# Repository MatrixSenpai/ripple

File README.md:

# Ripple

A small temperature box featuring a small led display and neopixel ring.

SW licensed under MIT license.
HW licensed under CC BY-SA.

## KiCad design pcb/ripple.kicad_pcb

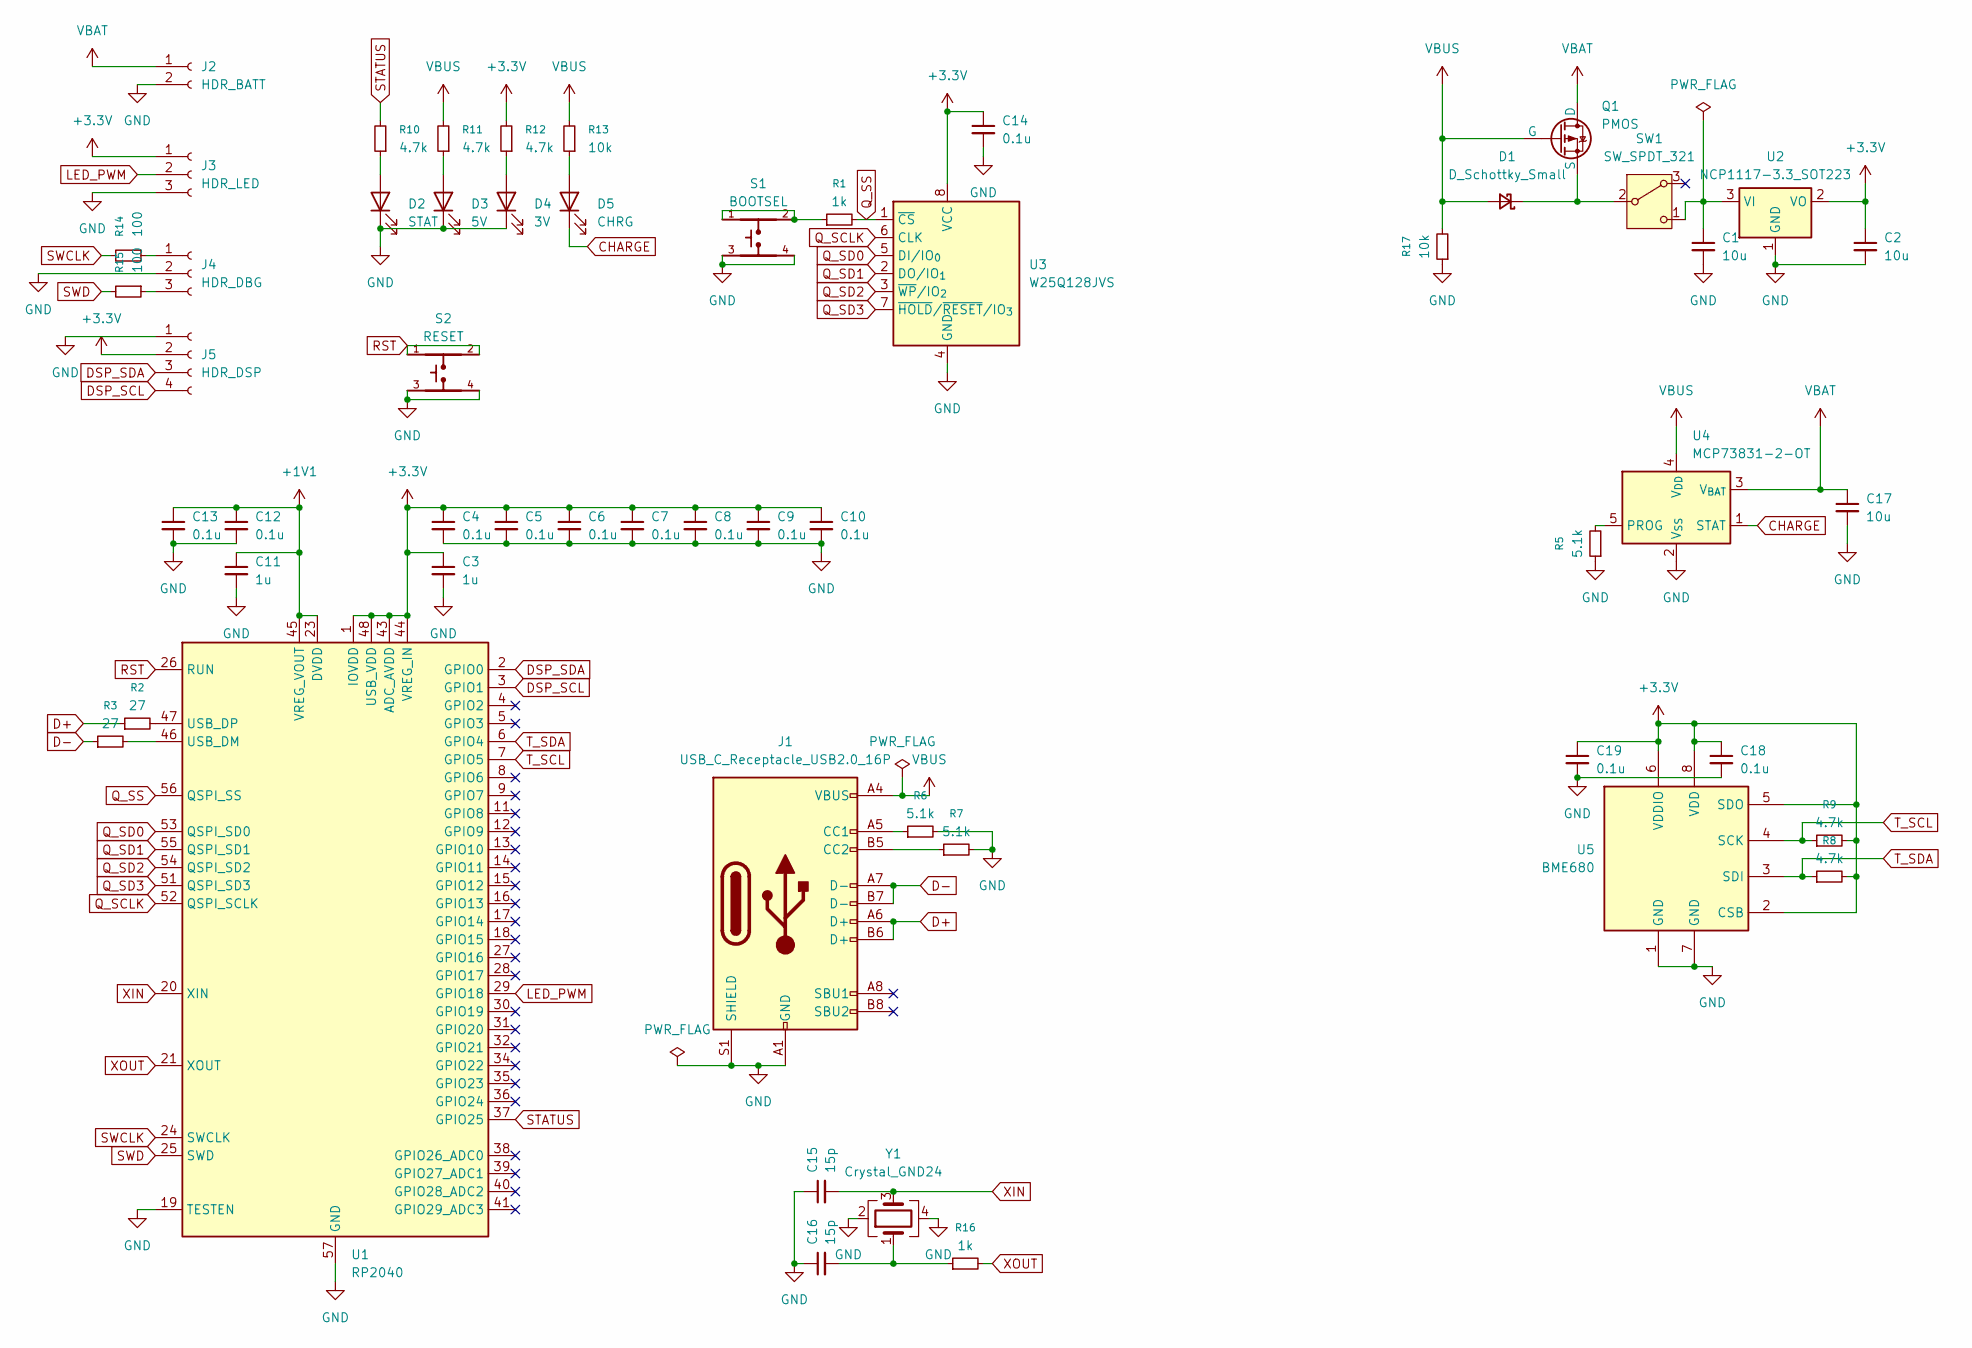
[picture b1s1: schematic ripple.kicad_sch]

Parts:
C1, C2, C17: 10u; C_0603_1608Metric_Pad1.08x0.95mm_HandSolder
C3, C11: 1u; C_0603_1608Metric_Pad1.08x0.95mm_HandSolder
C4, C5, C6, C7, C8, C9, C10, C12, C13, C14, C18, C19: 0.1u; C_0603_1608Metric_Pad1.08x0.95mm_HandSolder
C15, C16: 15p; C_0603_1608Metric_Pad1.08x0.95mm_HandSolder
D1: D_Schottky_Small; D_SOD-323_HandSoldering
D2: STAT; LED_0805_2012Metric_Pad1.15x1.40mm_HandSolder
D3: 5V; LED_0805_2012Metric_Pad1.15x1.40mm_HandSolder
D4: 3V; LED_0805_2012Metric_Pad1.15x1.40mm_HandSolder
D5: CHRG; LED_0805_2012Metric_Pad1.15x1.40mm_HandSolder
J1: USB_C_Receptacle_USB2.0_16P; USB_C_Receptacle_GCT_USB4105-xx-A_16P_TopMnt_Horizontal
J2: HDR_BATT; JST_PH_B2B-PH-K_1x02_P2.00mm_Vertical
J3: HDR_LED; PinSocket_1x03_P2.54mm_Vertical
J4: HDR_DBG; PinSocket_1x03_P2.54mm_Vertical
J5: HDR_DSP; PinSocket_1x04_P2.54mm_Vertical
Q1: PMOS; SOT-23-3
R1, R16: 1k; R_0603_1608Metric_Pad0.98x0.95mm_HandSolder
R2, R3: 27; R_0603_1608Metric_Pad0.98x0.95mm_HandSolder
R5, R6, R7: 5.1k; R_0603_1608Metric_Pad0.98x0.95mm_HandSolder
R8, R9, R10, R11, R12: 4.7k; R_0603_1608Metric_Pad0.98x0.95mm_HandSolder
R13, R17: 10k; R_0603_1608Metric_Pad0.98x0.95mm_HandSolder
R14, R15: 100; R_0603_1608Metric_Pad0.98x0.95mm_HandSolder
S1: BOOTSEL; SW_SKRPACE010
S2: RESET; SW_SKRPACE010
SW1: SW_SPDT_321; SW3_JSX08001SAQNL_CNK
U1: RP2040; QFN-56-1EP_7x7mm_P0.4mm_EP3.2x3.2mm
U2: NCP1117-3.3_SOT223; SOT-223-3_TabPin2
U3: W25Q128JVS; SOIC-8_5.3x5.3mm_P1.27mm
U4: MCP73831-2-OT; SOT-23-5
U5: BME680; Bosch_LGA-8_3x3mm_P0.8mm_ClockwisePinNumbering
Y1: Crystal_GND24; Crystal_SMD_Abracon_ABM8G-4Pin_3.2x2.5mm

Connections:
+1V1: C11.1, C12.1, C13.1, U1.23 (DVDD), U1.45 (VREG_VOUT), U1.50 (DVDD)
+3.3V: C2.1, C3.1, C4.1, C5.1, C6.1, C7.1, C8.1, C9.1, C10.1, C14.1, C18.1, C19.1, J3.1, J5.2, R8.2, R9.2, R12.2, U1.1 (IOVDD), U1.10 (IOVDD), U1.22 (IOVDD), U1.33 (IOVDD), U1.42 (IOVDD), U1.43 (ADC_AVDD), U1.44 (VREG_IN), U1.48 (USB_VDD), U1.49 (IOVDD), U2.2 (VO), U3.8 (VCC), U5.2 (CSB), U5.5 (SDO), U5.6 (VDDIO), U5.8 (VDD)
CHARGE: D5.1 (K), U4.1 (STAT)
D+: J1.A6 (D+), J1.B6 (D+), R2.1
D-: J1.A7 (D-), J1.B7 (D-), R3.1
DSP_SCL: J5.4, U1.3 (GPIO1)
DSP_SDA: J5.3, U1.2 (GPIO0)
GND: C1.2, C2.2, C3.2, C4.2, C5.2, C6.2, C7.2, C8.2, C9.2, C10.2, C11.2, C12.2, C13.2, C14.2, C15.1, C16.1, C17.2, C18.2, C19.2, D2.1 (K), D3.1 (K), D4.1 (K), J1.A1 (GND), J1.A12 (GND), J1.B1 (GND), J1.B12 (GND), J1.S1 (SHIELD), J2.2, J3.3, J4.2, J5.1, R5.1, R6.2, R7.2, R17.1, S1.3, S1.4, S2.3, S2.4, U1.19 (TESTEN), U1.57 (GND), U2.1 (GND), U3.4 (GND), U4.2 (V_{SS}), U5.1 (GND), U5.7 (GND), Y1.2, Y1.4
LED_PWM: J3.2, U1.29 (GPIO18)
unnamed: C16.2, R16.1, Y1.1
unnamed: D1.1 (K), Q1.3 (S), SW1.2 (B)
unnamed: D2.2 (A), R10.1
unnamed: D3.2 (A), R11.1
unnamed: D4.2 (A), R12.1
unnamed: D5.2 (A), R13.1
unnamed: J1.A5 (CC1), R6.1
unnamed: J1.B5 (CC2), R7.1
unnamed: J4.1, R14.1
unnamed: J4.3, R15.1
unnamed: R1.1, S1.1, S1.2
unnamed: C1.1, SW1.1 (C), U2.3 (VI)
unnamed: R3.2, U1.46 (USB_DM)
unnamed: R2.2, U1.47 (USB_DP)
unnamed: R5.2, U4.5 (PROG)
Q_SCLK: U1.52 (QSPI_SCLK), U3.6 (CLK)
Q_SD0: U1.53 (QSPI_SD0), U3.5 (DI/IO_{0})
Q_SD1: U1.55 (QSPI_SD1), U3.2 (DO/IO_{1})
Q_SD2: U1.54 (QSPI_SD2), U3.3 (~WP/IO_{2})
Q_SD3: U1.51 (QSPI_SD3), U3.7 (~HOLD/~RESET/IO_{3})
Q_SS: R1.2, U1.56 (QSPI_SS), U3.1 (~CS)
RST: S2.1, S2.2, U1.26 (RUN)
STATUS: R10.2, U1.37 (GPIO25)
SWCLK: R14.2, U1.24 (SWCLK)
SWD: R15.2, U1.25 (SWD)
T_SCL: R9.1, U1.7 (GPIO5), U5.4 (SCK)
T_SDA: R8.1, U1.6 (GPIO4), U5.3 (SDI)
VBAT: C17.1, J2.1, Q1.1 (D), U4.3 (V_{BAT})
VBUS: D1.2 (A), J1.A4 (VBUS), J1.A9 (VBUS), J1.B4 (VBUS), J1.B9 (VBUS), Q1.2 (G), R11.2, R13.2, R17.2, U4.4 (V_{DD})
XIN: C15.2, U1.20 (XIN), Y1.3
XOUT: R16.2, U1.21 (XOUT)

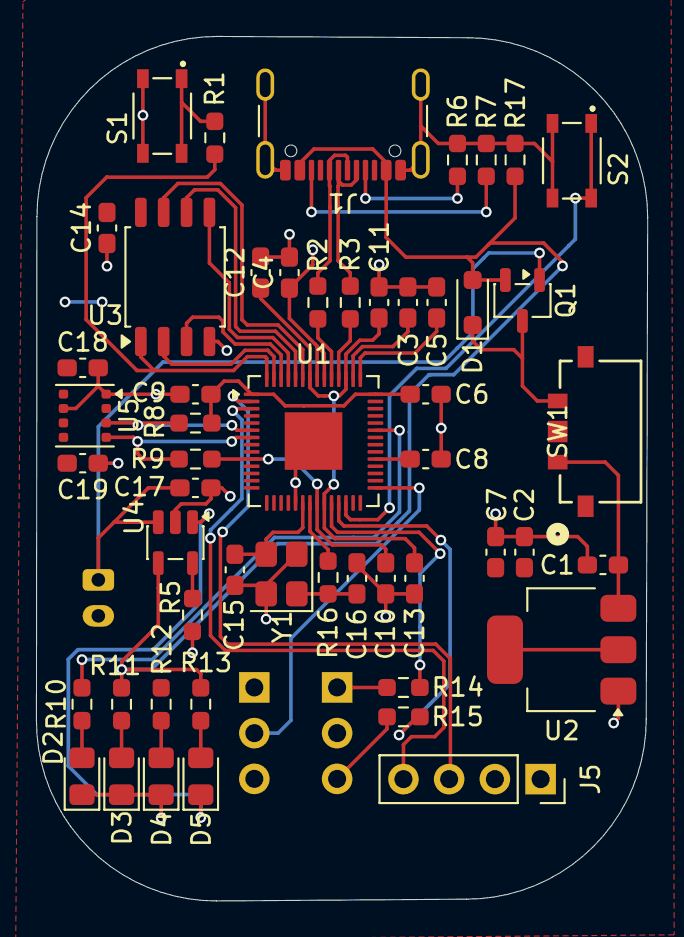
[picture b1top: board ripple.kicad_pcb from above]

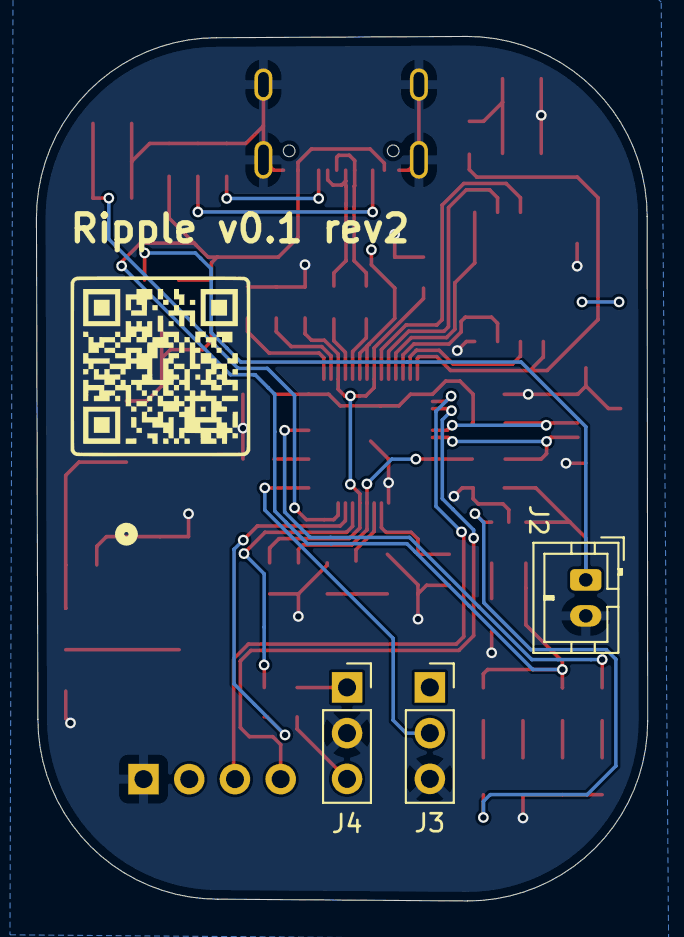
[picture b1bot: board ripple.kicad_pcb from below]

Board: 2 copper layers, 34.0 x 48.0 mm, 55 parts (3 on the bottom side), 40 nets.

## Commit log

2025-05-17 hw license and readme
2025-05-17 lic stuff
2025-05-17 Rename LICENSE.SW.txt to LICENSE-SW.txt
2025-05-17 Rename LICENSE.HW.txt to LICENSE-HW.txt
2025-05-21 adding box design
2025-05-21 restructuring to be more clean
2025-05-22 adding start of pcb design
2025-11-21 initial refactor commit of pcb
